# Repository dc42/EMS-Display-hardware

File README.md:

# EMS-Display-hardware

This repository holds the harware design files for my energy management system touch screen display and control.

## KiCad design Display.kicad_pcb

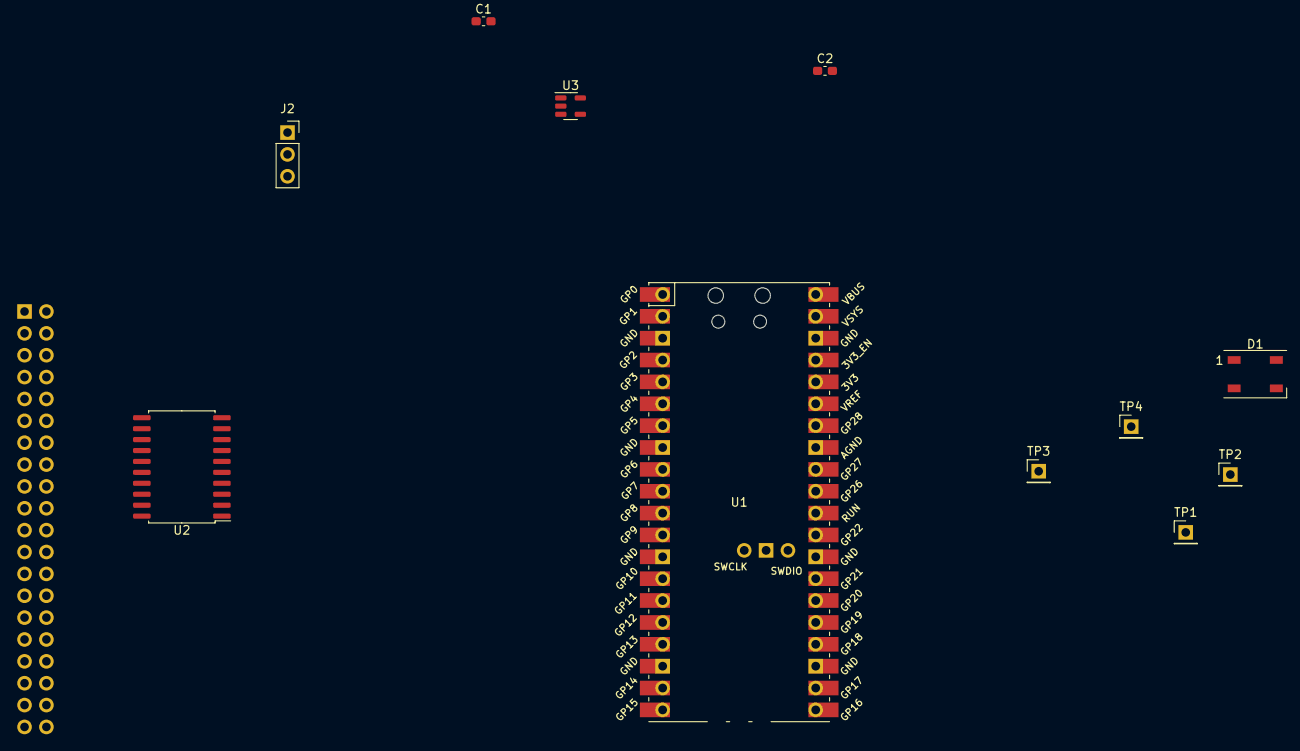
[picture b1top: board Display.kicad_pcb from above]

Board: 2 copper layers, 12 parts (1 on the bottom side), 38 nets, no tracks yet.

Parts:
C1, C2: 100n; C_0603_1608Metric_Pad1.08x0.95mm_HandSolder
D1: WS2812B; LED_WS2812B_PLCC4_5.0x5.0mm_P3.2mm
J1: TFT; PinSocket_2x20_P2.54mm_Vertical
J2: PIR; PinSocket_1x03_P2.54mm_Vertical
TP1: GP22; PinHeader_1x01_P2.54mm_Vertical
TP2: GP26; PinHeader_1x01_P2.54mm_Vertical
TP3: GP27; PinHeader_1x01_P2.54mm_Vertical
TP4: GP28; PinHeader_1x01_P2.54mm_Vertical
U1: PicoW; RPi_PicoW_SMD_TH
U2: 74HC573; SOIC-20W_7.5x12.8mm_P1.27mm
U3: 74AHCT1G125; SOT-23-5

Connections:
+3.3V: C1.1, J1.3, J2.1, U1.36 (3V3), U2.20 (VCC)
+5V: C2.1, D1.1 (VDD), J1.35, U1.40 (VBUS), U3.5 (VCC)
/CS: J1.29, U1.16 (GPIO12)
/D0: J1.2, U2.12 (Q7)
/D1: J1.4, U2.13 (Q6)
/D2: J1.6, U2.14 (Q5)
/D3: J1.8, U2.15 (Q4)
/D4: J1.10, U2.16 (Q3)
/D5: J1.12, U2.17 (Q2)
/D6: J1.14, U2.18 (Q1)
/D7: J1.16, U2.19 (Q0)
/D8: J1.13, U1.1 (GPIO0), U2.9 (D7)
/D9: J1.15, U1.2 (GPIO1), U2.8 (D6)
/D10: J1.17, U1.4 (GPIO2), U2.7 (D5)
/D11: J1.19, U1.5 (GPIO3), U2.6 (D4)
/D12: J1.21, U1.6 (GPIO4), U2.5 (D3)
/D13: J1.23, U1.7 (GPIO5), U2.4 (D2)
/D14: J1.25, U1.9 (GPIO6), U2.3 (D1)
/D15: J1.27, U1.10 (GPIO7), U2.2 (D0)
/PWM: J1.37, U1.19 (GPIO14)
/RD: J1.11, U1.12 (GPIO9)
/RS: J1.7, U1.15 (GPIO11)
/RST: J1.33, U1.17 (GPIO13)
/TCLK: J1.18, U1.24 (GPIO18)
/TCS: J1.20, U1.27 (GPIO21)
/TDIN: J1.22, U1.25 (GPIO19)
/TDO: J1.26, U1.26 (GPIO20)
/TIRQ: J1.28, U1.22 (GPIO17)
/WR: J1.9, U1.14 (GPIO10)
GND: C1.2, C2.2, D1.3 (VSS), J1.1, J2.3, U1.3 (GND), U1.8 (GND), U1.13 (GND), U1.18 (GND), U1.23 (GND), U1.28 (GND), U1.33 (AGND), U1.38 (GND), U2.1 (OE), U2.10 (GND), U3.1, U3.3 (GND)
unnamed: D1.4 (DIN), U3.4
unnamed: J2.2, U1.20 (GPIO15)
unnamed: TP1.1, U1.29 (GPIO22)
unnamed: TP2.1, U1.31 (GPIO26_ADC0)
unnamed: TP3.1, U1.32 (GPIO27_ADC1)
unnamed: TP4.1, U1.34 (GPIO28_ADC2)
unnamed: U1.11 (GPIO8), U2.11 (Load)
unnamed: U1.21 (GPIO16), U3.2

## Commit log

2022-12-01 Added display hardware schematic
2022-12-28 Added PDF schematic
